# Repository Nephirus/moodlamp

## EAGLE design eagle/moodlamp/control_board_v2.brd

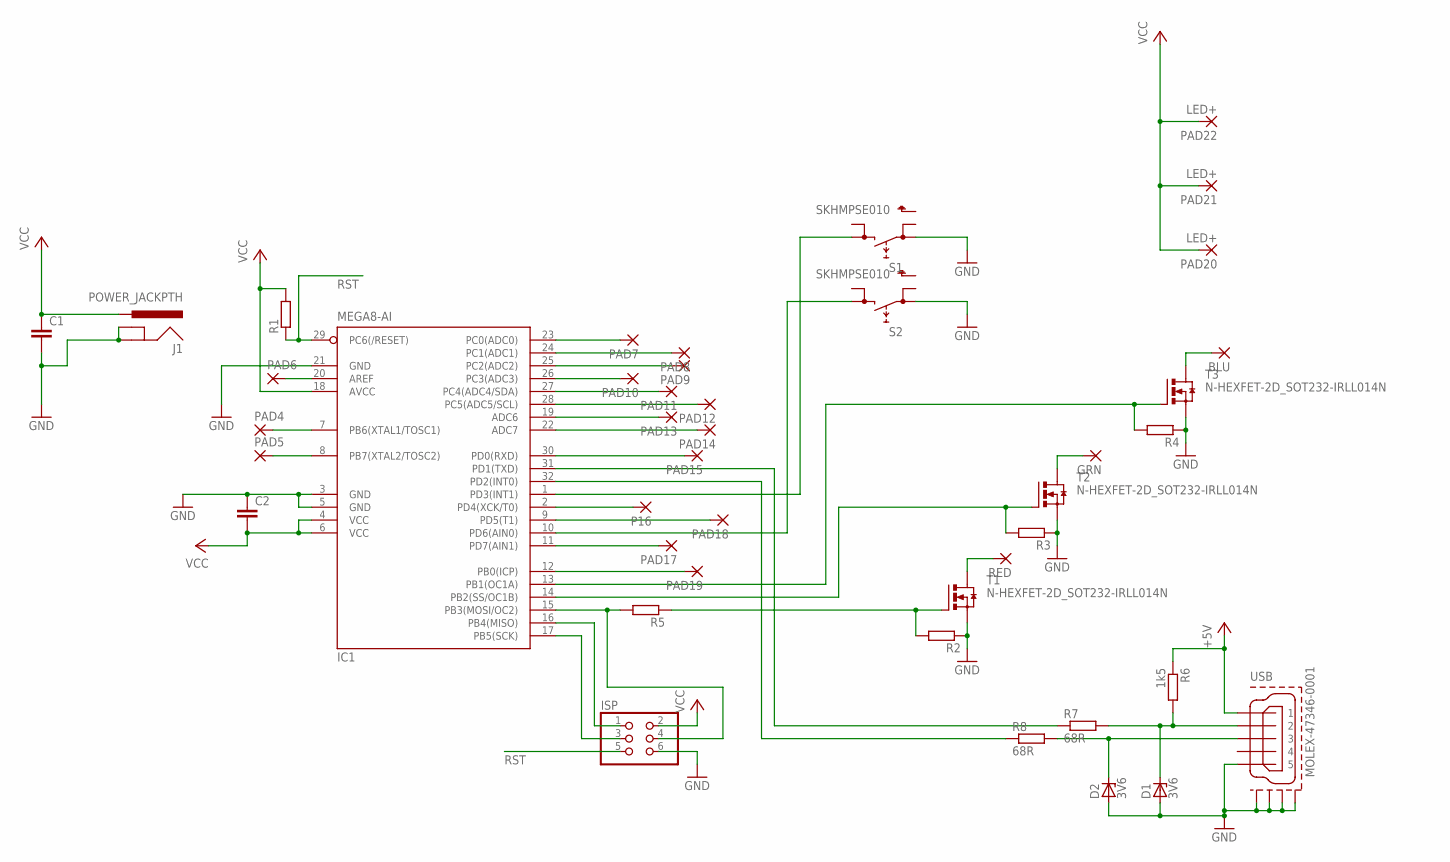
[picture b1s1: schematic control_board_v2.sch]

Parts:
BLU: 2,54/1,0
C1, C2: C-EUC0805; C0805
D1, D2: 3V6; SOD80C
GRN: 2,54/1,0
IC1: MEGA8-AI; TQFP32-08
ISP: PINHD-2X3; 2X03
J1: POWER_JACKPTH; POWER_JACK_PTH
P16: 1,6/0,9
PAD4, PAD5, PAD6, PAD7, PAD8, PAD9, PAD10, PAD11, PAD12, PAD13, PAD14, PAD15, PAD17, PAD18, PAD19: 1,6/0,9
PAD20, PAD21, PAD22: LED+; 2,54/1,0
R1, R2, R3, R4, R5: R-EU_R0805; R0805
R6: 1k5; R0805
R7, R8: 68R; R0805
RED: 2,54/1,0
S1, S2: SKHMPSE010; SKHMPXE010
T1, T2, T3: N-HEXFET-2D_SOT232-IRLL014N; SOT223
USB: MOLEX-47346-0001; MOLEX-47364-0001

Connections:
+5V: R6.1, USB.1
GND: C1.2, C2.1, D1.A, D2.A, IC1.3 (GND), IC1.5 (GND), IC1.21 (GND), ISP.6, J1.GND, J1.GNDBREAK, R2.1, R3.1, R4.1, S1.1 (1.1), S2.1 (1.1), T1.3 (S), T2.3 (S), T3.3 (S), USB.5, USB.GND1, USB.GND2, USB.GND3, USB.GND4
unnamed: IC1.16 (PB4(MISO)), ISP.1
unnamed: IC1.15 (PB3(MOSI/OC2)), ISP.4, R5.2
unnamed: RED.1, T1.2 (D), T1.4 (D)
unnamed: IC1.14 (PB2(SS/OC1B)), R3.2, T2.1 (G)
unnamed: GRN.1, T2.2 (D), T2.4 (D)
unnamed: IC1.13 (PB1(OC1A)), R4.2, T3.1 (G)
unnamed: BLU.1, T3.2 (D), T3.4 (D)
unnamed: IC1.10 (PD6(AIN0)), S2.3 (2.1)
unnamed: IC1.1 (PD3(INT1)), S1.3 (2.1)
unnamed: IC1.31 (PD1(TXD)), R7.1
unnamed: IC1.32 (PD2(INT0)), R8.1
unnamed: R2.2, R5.1, T1.1 (G)
unnamed: IC1.17 (PB5(SCK)), ISP.3
unnamed: IC1.20 (AREF), PAD6.1
unnamed: IC1.23 (PC0(ADC0)), PAD7.1
unnamed: IC1.24 (PC1(ADC1)), PAD8.1
unnamed: IC1.25 (PC2(ADC2)), PAD9.1
unnamed: IC1.26 (PC3(ADC3)), PAD10.1
unnamed: IC1.27 (PC4(ADC4/SDA)), PAD11.1
unnamed: IC1.28 (PC5(ADC5/SCL)), PAD12.1
unnamed: IC1.19 (ADC6), PAD13.1
unnamed: IC1.22 (ADC7), PAD14.1
unnamed: IC1.30 (PD0(RXD)), PAD15.1
unnamed: IC1.2 (PD4(XCK/T0)), P16.1
unnamed: IC1.11 (PD7(AIN1)), PAD17.1
unnamed: IC1.9 (PD5(T1)), PAD18.1
unnamed: IC1.12 (PB0(ICP)), PAD19.1
unnamed: IC1.7 (PB6(XTAL1/TOSC1)), PAD4.1
unnamed: IC1.8 (PB7(XTAL2/TOSC2)), PAD5.1
unnamed: D1.C, R6.2, R7.2, USB.2
unnamed: D2.C, R8.2, USB.3
RST: IC1.29 (PC6(/RESET)), ISP.5, R1.1
VCC: C1.1, C2.2, IC1.4 (VCC), IC1.6 (VCC), IC1.18 (AVCC), ISP.2, J1.PWR, PAD20.1, PAD21.1, PAD22.1, R1.2

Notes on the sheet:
RST

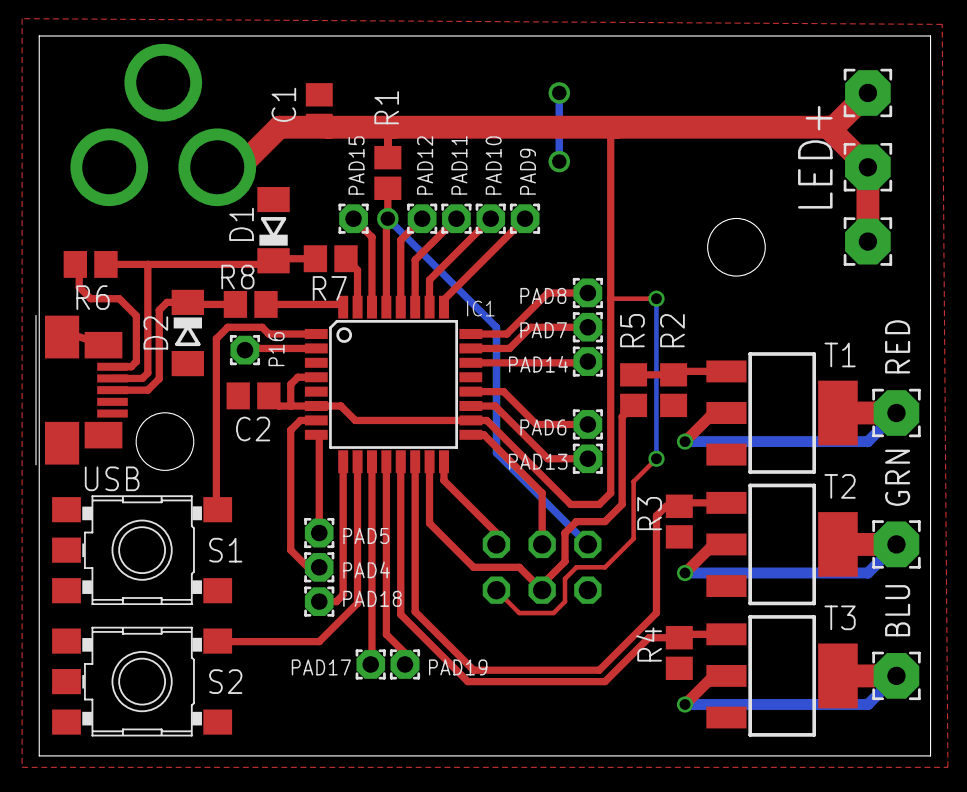
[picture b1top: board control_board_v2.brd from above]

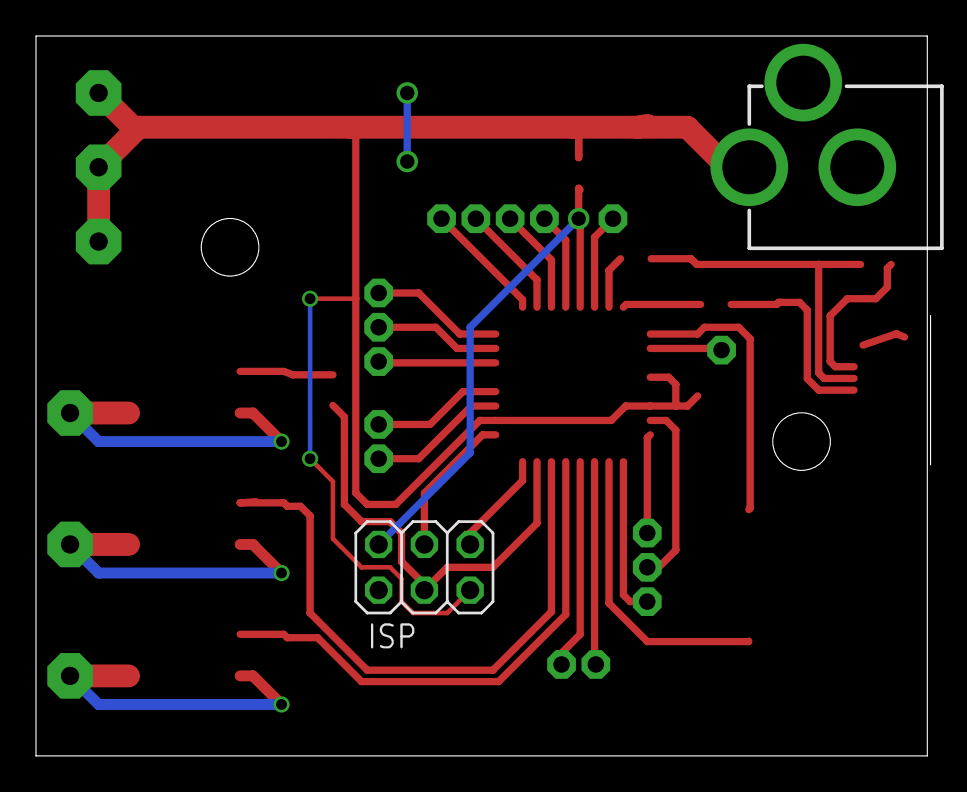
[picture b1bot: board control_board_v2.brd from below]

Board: 2 copper layers, 49.7 x 40.0 mm, 43 parts (2 on the bottom side), 35 nets.

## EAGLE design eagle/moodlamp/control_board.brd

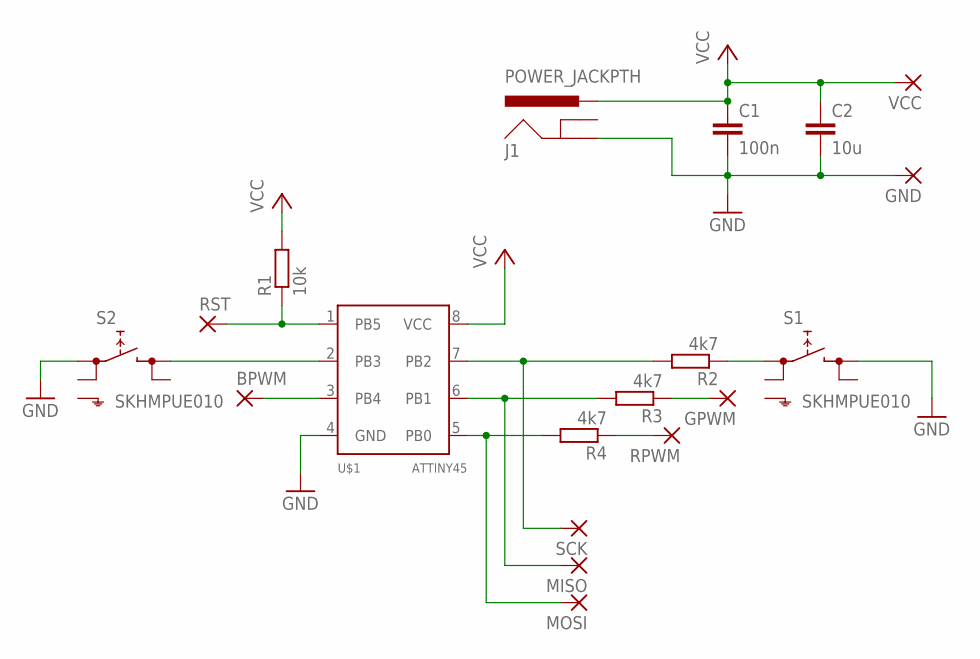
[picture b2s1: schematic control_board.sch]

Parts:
BPWM: SMD5; SMD2,54-5,08
C1: 100n; C1206
C2: 10u; C1206
GND: SMD5; SMD2,54-5,08
GPWM: SMD5; SMD2,54-5,08
J1: POWER_JACKPTH; POWER_JACK_PTH
MISO: SMD2; SMD1,27-2,54
MOSI: SMD2; SMD1,27-2,54
R1: 10k; R1206
R2, R3, R4: 4k7; R1206
RPWM: SMD5; SMD2,54-5,08
RST: SMD2; SMD1,27-2,54
S1, S2: SKHMPUE010; SKHMPXE010
SCK: SMD2; SMD1,27-2,54
U$1: ATTINY45; SOIC8
VCC: SMD5; SMD2,54-5,08

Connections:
GND: C1.2, C2.2, GND.1, J1.GND, S1.3 (2.1), S2.1 (1.1), U$1.4 (GND)
unnamed: S2.3 (2.1), U$1.2 (PB3)
unnamed: BPWM.1, U$1.3 (PB4)
unnamed: MISO.1, R3.2, U$1.6 (PB1)
unnamed: MOSI.1, R4.2, U$1.5 (PB0)
unnamed: R2.2, SCK.1, U$1.7 (PB2)
unnamed: R1.1, RST.1, U$1.1 (PB5)
unnamed: R2.1, S1.1 (1.1)
unnamed: GPWM.1, R3.1
unnamed: R4.1, RPWM.1
VCC: C1.1, C2.1, J1.PWR, R1.2, U$1.8 (VCC), VCC.1

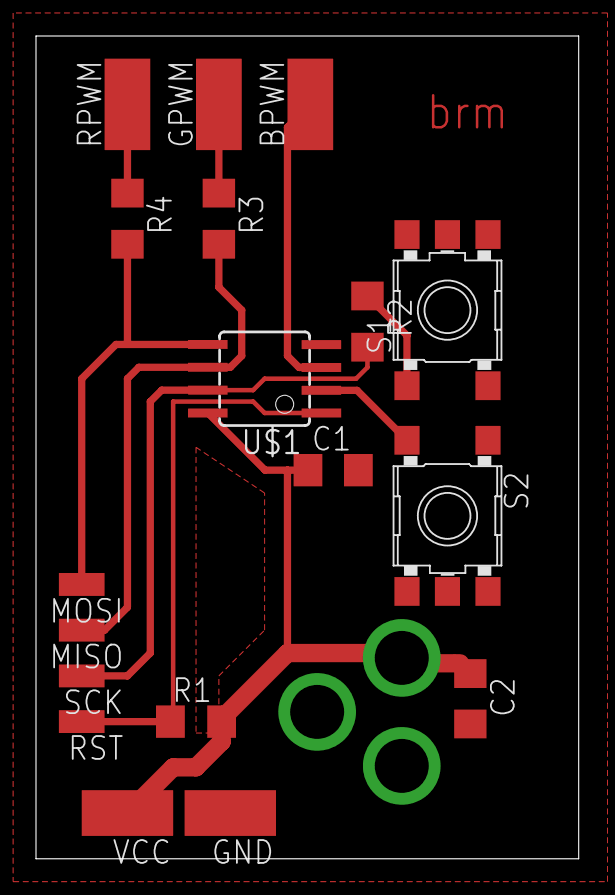
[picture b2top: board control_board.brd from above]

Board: 2 copper layers, 30.1 x 45.7 mm, 19 parts (1 on the bottom side), 11 nets.

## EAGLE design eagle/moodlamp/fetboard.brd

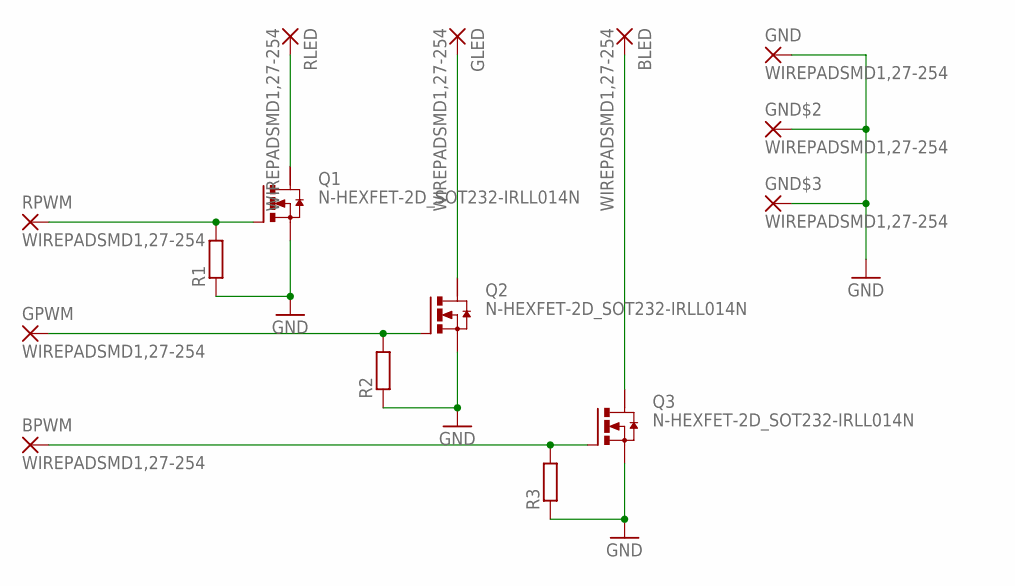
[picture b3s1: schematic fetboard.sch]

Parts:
BLED: WIREPADSMD1,27-254; SMD1,27-2,54
BPWM: WIREPADSMD1,27-254; SMD1,27-2,54
GLED: WIREPADSMD1,27-254; SMD1,27-2,54
GND: WIREPADSMD1,27-254; SMD1,27-2,54
GND$2, GND$3: WIREPADSMD1,27-254; SMD1,27-2,54
GPWM: WIREPADSMD1,27-254; SMD1,27-2,54
Q1, Q2, Q3: N-HEXFET-2D_SOT232-IRLL014N; SOT223
R1, R2, R3: R-EU_R1206; R1206
RLED: WIREPADSMD1,27-254; SMD1,27-2,54
RPWM: WIREPADSMD1,27-254; SMD1,27-2,54

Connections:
GND: GND.1, GND$2.1, GND$3.1, Q1.3 (S), Q2.3 (S), Q3.3 (S), R1.1, R2.1, R3.1
unnamed: Q1.1 (G), R1.2, RPWM.1
unnamed: GPWM.1, Q2.1 (G), R2.2
unnamed: BPWM.1, Q3.1 (G), R3.2
unnamed: Q1.2 (D), RLED.1
unnamed: GLED.1, Q2.2 (D)
unnamed: BLED.1, Q3.2 (D)

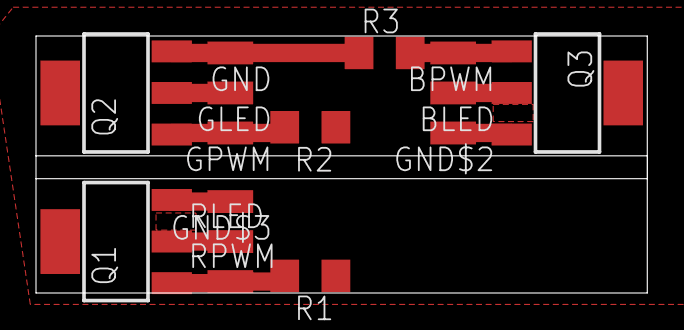
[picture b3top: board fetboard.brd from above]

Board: 2 copper layers, 34.0 x 14.3 mm, 15 parts (0 on the bottom side), 7 nets.

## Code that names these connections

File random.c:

#define F_CPU 1000000

#include <stdint.h>
#include <avr/interrupt.h>
#include <avr/io.h>
#include <util/delay.h>
#include <avr/sleep.h>


/*
 * CKSEL[3:0] = 0010 (default)
 * SUT = 10 (default)
 * CKDIV8 = 0 (default)
 * 
 * => f = 1 MHz
 * 
 */

void init(void);


enum { UP, DOWN };
volatile uint8_t r = 255;
volatile uint8_t g = 0;
volatile uint8_t b = 0;
volatile uint8_t dr, dg, db;

volatile uint8_t phase = 0;
volatile uint8_t cnt=0;

volatile uint8_t threshold;

volatile uint8_t input1 = 1;
volatile uint8_t input2 = 1;
volatile uint8_t input1_cnt=0;
volatile uint8_t input2_cnt=0;

const uint8_t thr[7] = {1, 2, 5, 10, 50, 200, 255};


ISR (TIM1_OVF_vect){
	
	if(++cnt>=threshold){
		switch (phase){
			case 0:
				if(++g == 255){
					phase++;
				}
				break;
			case 1:
				if(--r == 0){
					phase++;
				}
				break;
			case 2:
				if(++b == 240){
					phase++;
				}
				break;
			case 3:
				if(--g == 0){
					phase++;
				}
				break;
			case 4:
				if(++r == 255){
					phase++;
				}
				break;
			case 5:
				if(--b == 0){
					phase = 0;
				}
				break;
		}
		
		OCR1A = g;                
		OCR1B = b;
		OCR0A = r;
		cnt = 0;
	}
	
}


int main(void){
	init();
	uint8_t i=4;
	threshold = thr[i];

	while(1){
		if(((PINB & _BV(PB2))) == 0){
			if(i>0){
				threshold = thr[--i];
			}
			_delay_ms(500);
		}
		if(((PINB & _BV(PB3))) == 0){
			if(i<6){
				threshold = thr[++i];
			}
			_delay_ms(500);
		}
	}
	return 0;
}

void init(void){
	/* green - OCR1A - PB1 */
	TCCR1 = _BV(PWM1A) | _BV(COM1A1);
    TCCR1 |= _BV(CS11);
    OCR1A = 0;
    DDRB |= _BV (PB1);
	
	/* blue - OCR1B - PB4 */
	GTCCR = _BV(PWM1B) | _BV(COM1B1);
	OCR1B = 0;
	DDRB |= _BV (PB4);
	
	/* red - OCR0A - PB0 */
	TCCR0A = _BV(COM0A1) | _BV(WGM00) | _BV(WGM01);
	TCCR0B = _BV(CS01);
	OCR0A = 0;
	DDRB |= _BV(PB0);

	/* input buttons */
	PORTB |= _BV(PB2) | _BV(PB3);
	
    TIMSK = _BV (TOIE1);
    sei ();
}

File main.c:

/*
 *  Moodlamp v2 firmware
 *  Author: Nephirus <nephirus@nephirus.cz>
 *
 *  Moodlamp is a programmable RGB LED lamp driven by ATmega8A MCU.
 */

/*
 * Red      PB3 (OC2)
 * Green    PB2 (OC1A)
 * Blue     PB1 (OC1B)
 */

#define F_CPU 1000000UL

#include <stdint.h>
#include <avr/io.h>
#include <avr/interrupt.h>
#include <util/delay.h>


void init();
void clear_all();
void test_colors();
void rainbow_update();

volatile uint8_t r = 255;
volatile uint8_t g = 0;
volatile uint8_t b = 0;
volatile uint8_t state = 1;
volatile uint8_t rainbow_step = 20;    // rainbow step size in ms



void init(){
    // Set direction of LED pins to output
    DDRB |= (1<<DDB3) | (1<<DDB2) | (1<<DDB1);

    // Setup buttons
    DDRD |= (1<<PD6);   // S2 -> input
    PORTD |= (1<<PD6);  // enable internal pullup

    DDRD |= (1<<PD3);   // S1 -> input
    PORTD |= (1<<PD3);  // enable internal pullup


    // Configure Timer0 
    TIMSK |= (1<<TOIE0);
    TCCR0 |= (1<<CS02) | (1<<CS00);     // clk/1024
    
    // Configure Timer2 (red PWM)
    TCCR2 |= (1<<WGM21) | (1<<WGM20);   // Fast PWM mode
    TCCR2 |= (1<<COM21);   // Clear OC2 on Compare Match, set at bottom
    TCCR2 |= (1<<CS20);     // no prescaling

    // Configure Timer1 (green and blue PWM)
    TCCR1A |= (1<<WGM12) | (1<<WGM10);  // Fast PWM, 8-bit
    TCCR1A |= (1<<COM1A1) | (1<<COM1B1);    // Clear OC1{A,B} on Compare Match, set at bottom
    TCCR1B |= (1<<CS10);    // no prescaling
}

void clear_all(){
    PORTB &= ~((1<<PB3) | (1<<PB2) | (1<<PB1));
}

void test_colors(){
    PORTB |= (1<<PB3) | (1<<PB2) | (1<<PB1);
    _delay_ms(2500);
    clear_all();
    PORTB |= (1<<PB3);
    _delay_ms(2500);
    clear_all();
    PORTB |= (1<<PB2);
    _delay_ms(2500);
    clear_all();
    PORTB |= (1<<PB1);
    _delay_ms(2500);
    clear_all();
}

void rainbow_update(){
    OCR1A = g;
    OCR1B = b;
    OCR2 = r;
    switch (state){
        case 1:
            g++;
            if(g == 255)
                state++;
            break;
        case 2:
            r--;
            if(r == 0)
                state++;
            break;
        case 3:
            b++;
            if(b == 255)
                state++;
            break;
        case 4:
            g--;
            if(g == 0)
                state++;
            break;
        case 5:
            r++;
            if(r == 255)
                state++;
            break;
        case 6:
            b--;
            if(b == 0)
                state = 1;
            break;
    }
}

volatile uint8_t s1state = 0;
volatile uint8_t s1trig = 0;
volatile uint8_t s2state = 0;
volatile uint8_t s2trig = 0;

ISR(TIMER0_OVF_vect, ISR_NOBLOCK){
    rainbow_update();
    TCNT0 = 255 - rainbow_step;

    // input check - FIXME: checking interval should not depend on rainbow speed
    if(!(PIND & _BV(PD6))){
        s2state = 1;
    } else {
        s2state = 0;
        s2trig = 0;
    }

    if(!(PIND & _BV(PD3))){
        s1state = 1;
    } else {
        s1state = 0;
        s1trig = 0;
    }
}

int main(){
    init();
    sei();
    while (1){
        if(s2state && !s2trig){
            rainbow_step += 5;
            s2trig = 1;
        }
        if(s1state && !s1trig){
            rainbow_step -= 5;
            s1trig = 1;
        }
    }
    return 0;
}

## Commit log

2012-07-04 LED driver
2012-07-05 minor changes
2012-07-05 random.c: init()
2012-07-05 attiny45 library (soic8 package)
2012-07-05 control board schematic
2012-07-09 eagle epf
2012-07-17 random.c - test
2012-07-17 test2
2012-07-17 random.c - ok
2012-07-17 random.c - cleanup
2012-07-17 random.c - speed modes
2012-07-26 v2 electronics
2012-09-24 mounting holes, increased via drill size
2012-09-25 power jack fixed
2012-10-23 v2 prototype
2012-11-14 power jack orientation fixed
2012-11-14 isp connector orientation fixed
2012-11-14 drc cleanup
2012-11-21 Silkscreen
2012-11-21 RGB LED datasheet
2012-11-21 order no. removed
2012-11-21 final touch
2012-11-21 gerber files
2013-04-04 v2 - blink firmware
2013-04-04 red pwm
2013-04-04 green and blue pwm
2013-04-04 Rainbow
2013-04-04 Rainbow with variable cycle length
2013-04-07 rainbow - speed change

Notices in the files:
parts and their libraries:
SparkFun: Licensing: CC v3.0 Share-Alike You are welcome to use this library for commercial purposes.
